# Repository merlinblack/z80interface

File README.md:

z80interface
============

This is my C Atmega4809 code I an using to talk to a Z80 based hobby computer built on breadboards

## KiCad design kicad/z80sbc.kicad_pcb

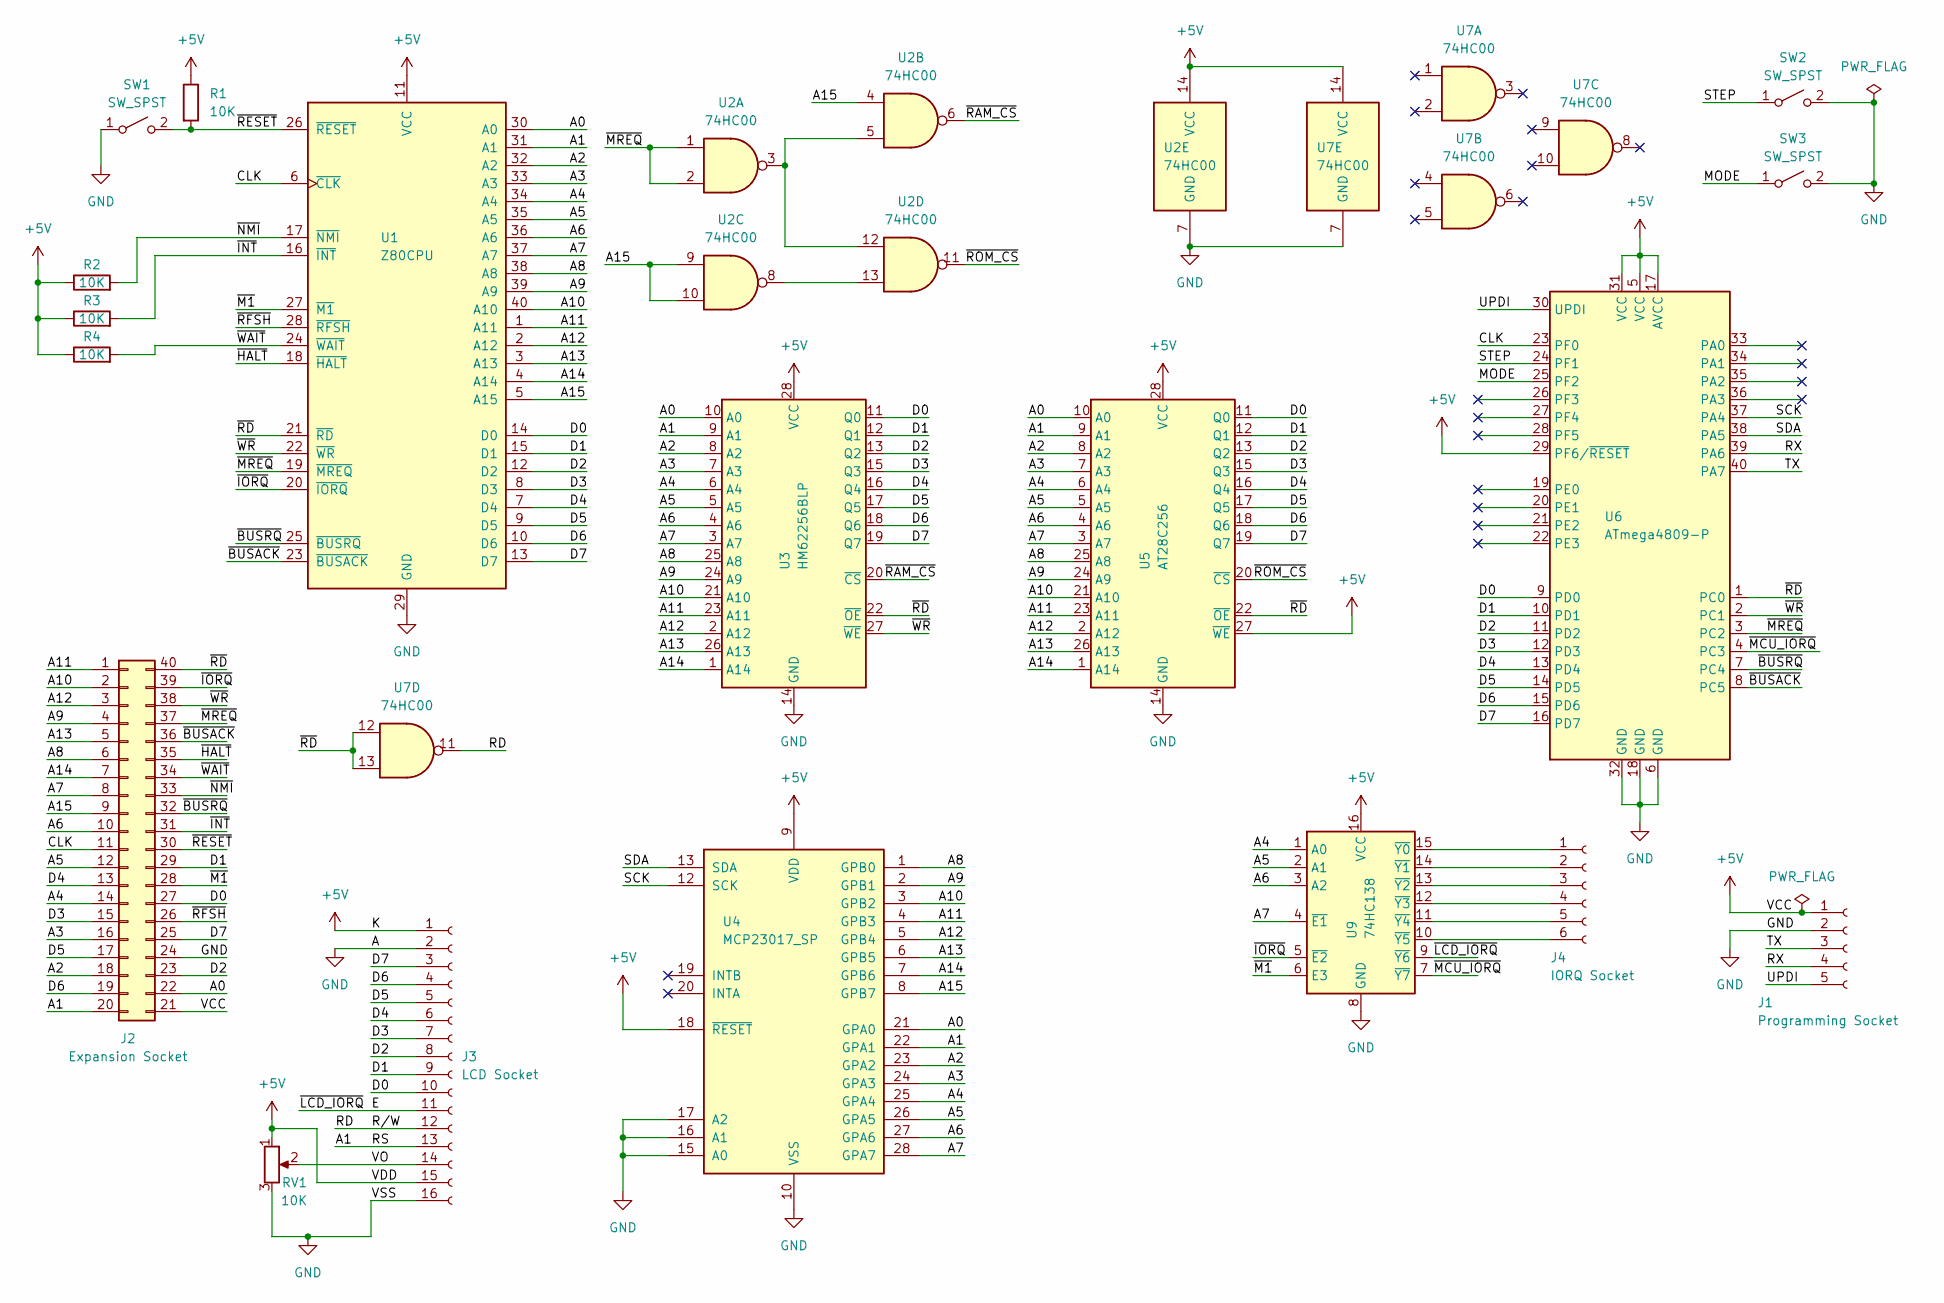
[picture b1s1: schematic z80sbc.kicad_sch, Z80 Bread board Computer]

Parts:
J1: Programming Socket; PinSocket_1x05_P2.54mm_Vertical
J2: Expansion Socket; PinSocket_2x20_P2.54mm_Vertical
J3: LCD Socket; PinSocket_1x16_P2.54mm_Vertical
J4: IORQ Socket; PinSocket_1x06_P2.54mm_Vertical
R1, R2, R3, R4: 10K; R_Axial_DIN0207_L6.3mm_D2.5mm_P10.16mm_Horizontal
RV1: 10K; Potentiometer_Bourns_3386P_Vertical
SW1, SW2, SW3: SW_SPST; SW_PUSH_6mm
U1: Z80CPU; DIP-40_W15.24mm
U2, U7: 74HC00; DIP-14_W7.62mm
U3: HM62256BLP; DIP-28_W15.24mm
U4: MCP23017_SP; DIP-28_W7.62mm
U5: AT28C256; DIP-28_W15.24mm
U6: ATmega4809-P; DIP-40_W15.24mm
U9: 74HC138; DIP-16_W7.62mm

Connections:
+5V: J1.1, J2.21, J3.1, J3.15, R1.1, R2.1, R3.1, R4.1, RV1.1, U1.11 (VCC), U2.14 (VCC), U3.28 (VCC), U4.9 (VDD), U4.18 (~RESET), U5.27 (~WE), U5.28 (VCC), U6.5 (VCC), U6.17 (AVCC), U6.29 (PF6/~RESET), U6.31 (VCC), U7.14 (VCC), U9.16 (VCC)
/A0: J2.22, U1.30 (A0), U3.10 (A0), U4.21 (GPA0), U5.10 (A0)
/A1: J2.20, J3.13, U1.31 (A1), U3.9 (A1), U4.22 (GPA1), U5.9 (A1)
/A2: J2.18, U1.32 (A2), U3.8 (A2), U4.23 (GPA2), U5.8 (A2)
/A3: J2.16, U1.33 (A3), U3.7 (A3), U4.24 (GPA3), U5.7 (A3)
/A4: J2.14, U1.34 (A4), U3.6 (A4), U4.25 (GPA4), U5.6 (A4), U9.1 (A0)
/A5: J2.12, U1.35 (A5), U3.5 (A5), U4.26 (GPA5), U5.5 (A5), U9.2 (A1)
/A6: J2.10, U1.36 (A6), U3.4 (A6), U4.27 (GPA6), U5.4 (A6), U9.3 (A2)
/A7: J2.8, U1.37 (A7), U3.3 (A7), U4.28 (GPA7), U5.3 (A7), U9.4 (~E1)
/A8: J2.6, U1.38 (A8), U3.25 (A8), U4.1 (GPB0), U5.25 (A8)
/A9: J2.4, U1.39 (A9), U3.24 (A9), U4.2 (GPB1), U5.24 (A9)
/A10: J2.2, U1.40 (A10), U3.21 (A10), U4.3 (GPB2), U5.21 (A10)
/A11: J2.1, U1.1 (A11), U3.23 (A11), U4.4 (GPB3), U5.23 (A11)
/A12: J2.3, U1.2 (A12), U3.2 (A12), U4.5 (GPB4), U5.2 (A12)
/A13: J2.5, U1.3 (A13), U3.26 (A13), U4.6 (GPB5), U5.26 (A13)
/A14: J2.7, U1.4 (A14), U3.1 (A14), U4.7 (GPB6), U5.1 (A14)
/A15: J2.9, U1.5 (A15), U2.4, U2.9, U2.10, U4.8 (GPB7)
/CLK: J2.11, U1.6 (~CLK), U6.23 (PF0)
/D0: J2.27, J3.10, U1.14 (D0), U3.11 (Q0), U5.11 (Q0), U6.9 (PD0)
/D1: J2.29, J3.9, U1.15 (D1), U3.12 (Q1), U5.12 (Q1), U6.10 (PD1)
/D2: J2.23, J3.8, U1.12 (D2), U3.13 (Q2), U5.13 (Q2), U6.11 (PD2)
/D3: J2.15, J3.7, U1.8 (D3), U3.15 (Q3), U5.15 (Q3), U6.12 (PD3)
/D4: J2.13, J3.6, U1.7 (D4), U3.16 (Q4), U5.16 (Q4), U6.13 (PD4)
/D5: J2.17, J3.5, U1.9 (D5), U3.17 (Q5), U5.17 (Q5), U6.14 (PD5)
/D6: J2.19, J3.4, U1.10 (D6), U3.18 (Q6), U5.18 (Q6), U6.15 (PD6)
/D7: J2.25, J3.3, U1.13 (D7), U3.19 (Q7), U5.19 (Q7), U6.16 (PD7)
/E: J3.11, U9.9 (~Y6)
/MODE: SW3.1 (A), U6.25 (PF2)
/RD: J3.12, U7.11
/RX: J1.4, U6.39 (PA6)
/SCK: U4.12 (SCK), U6.37 (PA4)
/SDA: U4.13 (SDA), U6.38 (PA5)
/STEP: SW2.1 (A), U6.24 (PF1)
/TX: J1.3, U6.40 (PA7)
/UPDI: J1.5, U6.30 (UPDI)
/VO: J3.14, RV1.2
/~BUSACK: J2.36, U1.23 (~BUSACK), U6.8 (PC5)
/~BUSRQ: J2.32, U1.25 (~BUSRQ), U6.7 (PC4)
/~HALT: J2.35, U1.18 (~HALT)
/~INT: J2.31, R3.2, U1.16 (~INT)
/~IORQ: J2.39, U1.20 (~IORQ), U9.5 (~E2)
/~M1: J2.28, U1.27 (~M1), U9.6 (E3)
/~MCU_IORQ: U6.4 (PC3), U9.7 (~Y7)
/~MREQ: J2.37, U1.19 (~MREQ), U2.1, U2.2, U6.3 (PC2)
/~NMI: J2.33, R2.2, U1.17 (~NMI)
/~RAM_CS: U2.6, U3.20 (~CS)
/~RD: J2.40, U1.21 (~RD), U3.22 (~OE), U5.22 (~OE), U6.1 (PC0), U7.12, U7.13
/~RESET: J2.30, R1.2, SW1.2 (B), U1.26 (~RESET)
/~RFSH: J2.26, U1.28 (~RFSH)
/~ROM_CS: U2.11, U5.20 (~CS)
/~WAIT: J2.34, R4.2, U1.24 (~WAIT)
/~WR: J2.38, U1.22 (~WR), U3.27 (~WE), U6.2 (PC1)
GND: J1.2, J2.24, J3.2, J3.16, RV1.3, SW1.1 (A), SW2.2 (B), SW3.2 (B), U1.29 (GND), U2.7 (GND), U3.14 (GND), U4.10 (VSS), U4.15 (A0), U4.16 (A1), U4.17 (A2), U5.14 (GND), U6.6 (GND), U6.18 (GND), U6.32 (GND), U7.7 (GND), U9.8 (GND)
unnamed: U2.3, U2.5, U2.12
unnamed: U2.8, U2.13
unnamed: J4.6, U9.10 (~Y5)
unnamed: J4.5, U9.11 (~Y4)
unnamed: J4.4, U9.12 (~Y3)
unnamed: J4.3, U9.13 (~Y2)
unnamed: J4.2, U9.14 (~Y1)
unnamed: J4.1, U9.15 (~Y0)

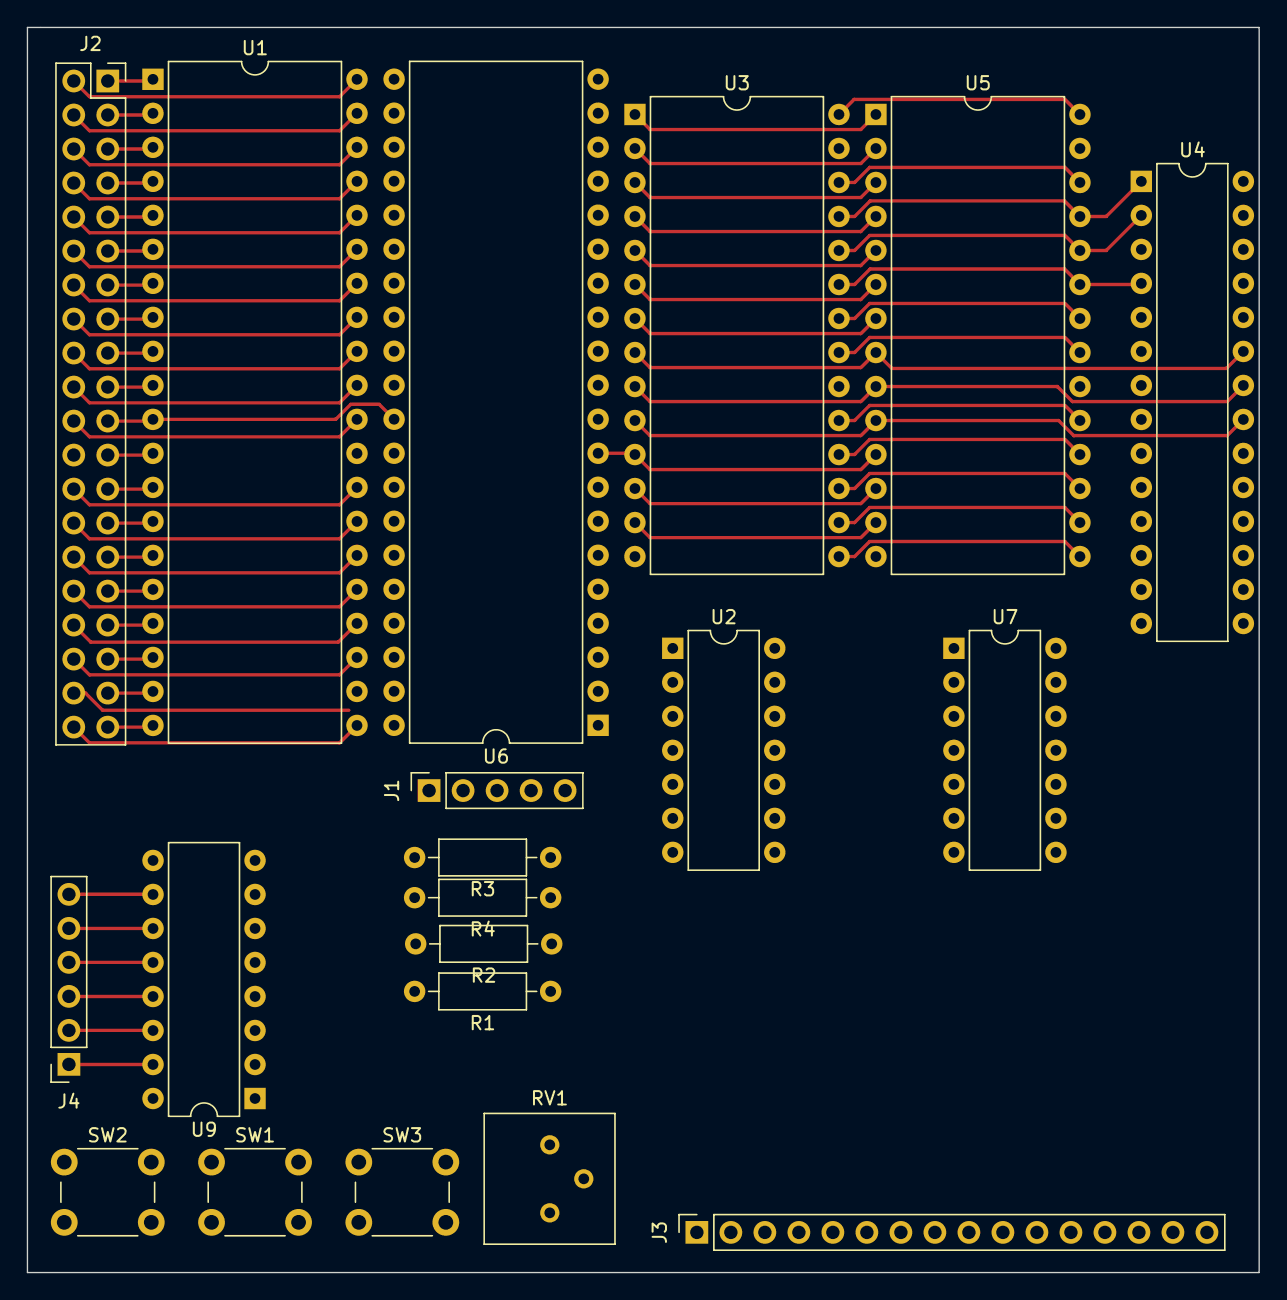
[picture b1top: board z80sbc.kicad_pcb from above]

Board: 2 copper layers, 92.0 x 93.0 mm, 20 parts (0 on the bottom side), 61 nets.

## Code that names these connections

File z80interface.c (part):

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#define WR_PORT PORTC
#define WR_PIN_bm PIN1_bm

#define MREQ_PORT PORTC
#define MREQ_PIN_bm PIN2_bm

#define IORQ_PORT PORTC
#define IORQ_PIN_bm PIN3_bm

#define BUSREQ_PORT PORTC
#define BUSREQ_PIN_bm PIN4_bm

#define BUSACK_PORT PORTC
#define BUSACK_PIN_bm PIN5_bm

#define MAX_MESSAGE 64
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	DATA_PORT.DIRCLR = 0xFF;
	RD_PORT.DIRCLR = RD_PIN_bm;
	WR_PORT.DIRCLR = WR_PIN_bm;
	MREQ_PORT.DIRCLR = MREQ_PIN_bm;
	IORQ_PORT.DIRCLR = IORQ_PIN_bm;
	IORQ_PORT.PIN3CTRL |= PORT_ISC_FALLING_gc;
	BUSREQ_PORT.DIRSET = BUSREQ_PIN_bm;
	BUSREQ_PORT.OUTSET = BUSREQ_PIN_bm;		// Active low - i.e. turn it off.
	BUSACK_PORT.DIRCLR = BUSACK_PIN_bm;
}

void delay(uint16_t delay)
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void waitForBus()
{
	BUSREQ_PORT.OUTCLR = BUSREQ_PIN_bm;
	while( BUSACK_PORT.IN & BUSACK_PIN_bm)
		CLOCK_PORT.OUTTGL = CLOCK_PIN_bm;
}

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
	/* init bus */
	mcp23017_set_direction(MCP23017_ADDR, 0x0000);
	MREQ_PORT.DIRSET = MREQ_PIN_bm;
	IORQ_PORT.DIRSET = IORQ_PIN_bm;
	WR_PORT.DIRSET = WR_PIN_bm;
	RD_PORT.DIRSET = RD_PIN_bm;
	/* active low - make them high */
	MREQ_PORT.OUTSET = MREQ_PIN_bm;
	IORQ_PORT.OUTSET = IORQ_PIN_bm;
	WR_PORT.OUTSET = WR_PIN_bm;
	RD_PORT.OUTSET = RD_PIN_bm;
}
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{
	WR_PORT.DIRCLR = WR_PIN_bm;
	RD_PORT.DIRCLR = RD_PIN_bm;
	MREQ_PORT.DIRCLR = MREQ_PIN_bm;
	IORQ_PORT.DIRCLR = IORQ_PIN_bm;
	DATA_PORT.DIRCLR = 0xFF;
	mcp23017_set_direction(MCP23017_ADDR, 0xFFFF);

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{
	DATA_PORT.DIRCLR = 0xFF;
	mcp23017_write_both(MCP23017_ADDR, address);
	MREQ_PORT.OUTCLR = MREQ_PIN_bm;
	RD_PORT.OUTCLR = RD_PIN_bm;

	_delay_us(1);
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	uint8_t data = DATA_VPORT.IN;

	RD_PORT.OUTSET = RD_PIN_bm;
	MREQ_PORT.OUTSET = MREQ_PIN_bm;

	return data;
}
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{
	DATA_PORT.DIRSET = 0xFF;
	mcp23017_write_both(MCP23017_ADDR, address);
	MREQ_PORT.OUTCLR = MREQ_PIN_bm;

	DATA_VPORT.OUT = data;

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	_delay_us(1);
	WR_PORT.OUTSET = WR_PIN_bm;

	MREQ_PORT.OUTSET = MREQ_PIN_bm;
}

char command[MAX_COMMAND_LEN];
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
		if (mcp23017_read_both(MCP23017_ADDR) == address)
		{
			if ( !(MREQ_PORT.IN & MREQ_PIN_bm) && !(RD_PORT.IN & RD_PIN_bm))
			{
				printf("Got address - stopping\r\n");
				done = true;
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			uint16_t address = mcp23017_read_both(MCP23017_ADDR);
			bool readBit = RD_PORT.IN & RD_PIN_bm;
			bool writeBit = WR_PORT.IN & WR_PIN_bm;
			bool mreqBit = MREQ_PORT.IN & MREQ_PIN_bm;
			bool iorqBit = IORQ_PORT.IN & IORQ_PIN_bm;
			bool busReqBit = BUSREQ_PORT.IN & BUSREQ_PIN_bm;
			bool busAckBit = BUSACK_PORT.IN & BUSACK_PIN_bm;

			printf("%10lu - %4s %7s %04x %02x [%c%c%c%c%c%c] '%c' [%-32s] > %-32s\r",
					currentTime, 
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
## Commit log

2022-07-05 Refactor and add more pin defs
2022-07-07 Add recieve ring buffer for usart and get char function
2022-07-07 Memory reading experiment
2022-07-07 Add photo of computer
2022-07-12 Getting XON/XOFF to work under Linux
    Turns out the USB serial ignores XON/XOFF, so you have to do it
    yourself.
2022-07-12 Fine tune XON/XOFF
2022-07-13 Command line interface beginings.
2022-07-13 Hex file upload!
2022-07-15 Add RunTo command
2022-07-15 Add my z80 code
2022-07-25 LCD code!
2022-07-26 Automate mybios.inc generation
2022-07-31 KiCad and move lcd code to rom
2022-08-01 Schematic as built :-)
2022-08-01 PCB Work in progress
2022-08-07 HW bugfix (lcd E line) and support RAM as fake ROM
2022-08-18 Add missing ret
